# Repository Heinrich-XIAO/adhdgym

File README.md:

# adhdgym
adhdgym is a simple ultrasonic distance sensor that relays the distance to your computer at its simplest. It can be attatched to your cable machine to track your workouts. It comes with a web app that gamifies the experience of hitting your home gym. I made this because I kept being lazy in my workouts and not actualy liting the full amount, so having an app to keep track of this, and gamify this will probaby motivate me, or at least thats how i justify this.

## CAD

## PCB

## Schematics

## Client

## Build

https://youtube.com/shorts/1jzXrwt-IXw

## BOM
 - PCB and Case (I can 3D print myself)  $19.60 for pcb with jlc
 - 1x4 DuPont connector 2.54mm Socket (i think i have some)
 - Seeed XIAO ESP32-C3 https://www.seeedstudio.com/Seeed-XIAO-ESP32C3-p-5431.html  $24.40 (why is shipping so expensive :sob:)
 - DHT11 https://lcsc.com/product-detail/Temperature-and-Humidity-Sensor_Aosong-Guangzhou-Elec-DHT11_C117051.html?s_z=n_dht11 $18.43 (how is the cheapest shipping still $11.44 :sob::sob:)
 - HC-SR04 Module https://www.aliexpress.com/item/1005008259734214.html (if this link rots one day, just make sure to get one that has the pins on the non-speaker side) $2.65

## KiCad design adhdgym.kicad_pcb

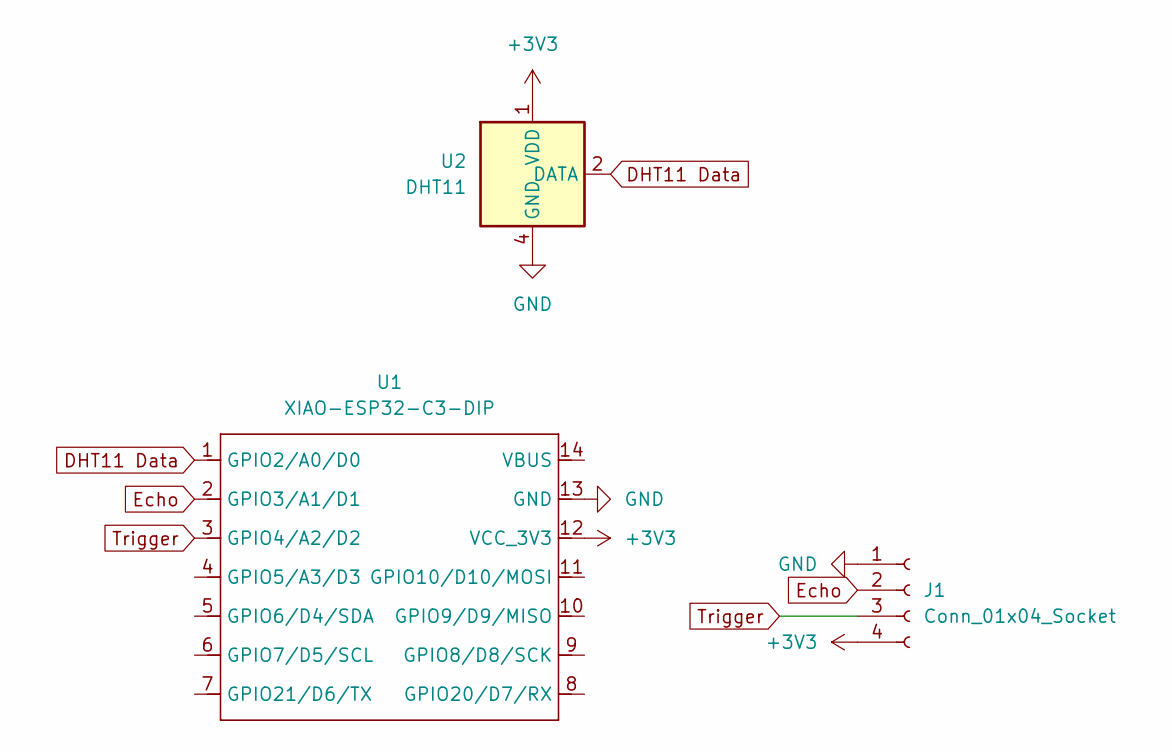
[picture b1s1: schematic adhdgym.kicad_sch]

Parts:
J1: Conn_01x04_Socket; PinSocket_1x04_P2.54mm_Vertical
U1: XIAO-ESP32-C3-DIP; MCU_Seeed_ESP32C3
U2: DHT11; Aosong_DHT11_5.5x12.0_P2.54mm

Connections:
+3V3: J1.4, U1.12 (VCC_3V3), U2.1 (VDD)
DHT11 Data: U1.1 (GPIO2/A0/D0), U2.2 (DATA)
Echo: J1.2, U1.2 (GPIO3/A1/D1)
GND: J1.1, U1.13 (GND), U2.4 (GND)
Trigger: J1.3, U1.3 (GPIO4/A2/D2)

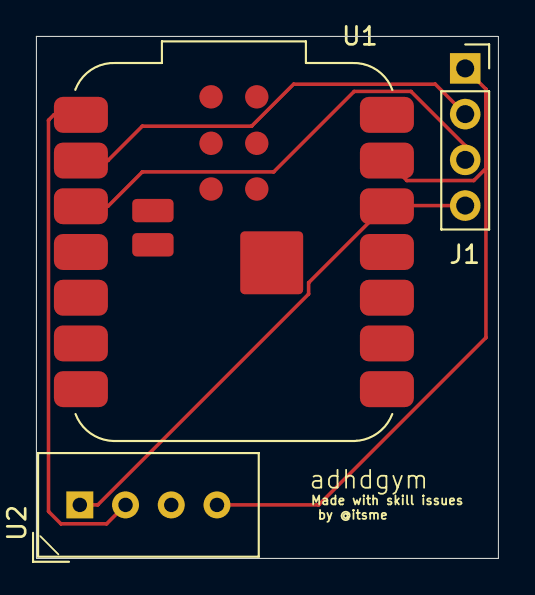
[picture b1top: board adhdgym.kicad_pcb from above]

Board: 2 copper layers, 25.7 x 29.0 mm, 3 parts (0 on the bottom side), 5 nets.

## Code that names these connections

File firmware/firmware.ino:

#include <Arduino.h>
#include <DHT.h>
#include <BLEDevice.h>
#include <BLEServer.h>
#include <BLEUtils.h>
#include <BLE2902.h>

// Pins
#define DHTPIN       2   // GPIO2 (A0/D0)
#define DHTTYPE      DHT11
#define TRIG_PIN     4   // GPIO4 (A2/D2)
#define ECHO_PIN     3   // GPIO3 (A1/D1)

// BLE UUIDs
#define SERVICE_UUID        "1f45750b-771b-460b-92ca-fdc00d263aee"
#define CHARACTERISTIC_UUID "064805b7-1272-436b-9683-a94509066057"

// Globals
DHT dht(DHTPIN, DHTTYPE);
BLECharacteristic* pCharacteristic;

// Speed of sound
// = 331 + 0.6 * T (in m/s), T = temp in C (proud canadian)
float calculateDistance(float temperatureC) {
  digitalWrite(TRIG_PIN, LOW);
  delayMicroseconds(2);
  digitalWrite(TRIG_PIN, HIGH);
  delayMicroseconds(10);
  digitalWrite(TRIG_PIN, LOW);

  long duration = pulseIn(ECHO_PIN, HIGH, 30000);
  float speed_of_sound = 331.0 + 0.6 * temperatureC; // m/s
  float distance_cm = (duration / 1e6) * speed_of_sound * 100 / 2;

  return distance_cm;
}

void setup() {
  Serial.begin(115200);
  delay(1000);

  // Init DHT
  dht.begin();

  // Init Ultrasonic pins
  pinMode(TRIG_PIN, OUTPUT);
  pinMode(ECHO_PIN, INPUT);

  // Init BLE
  BLEDevice::init("adhdgym");
  BLEServer *pServer = BLEDevice::createServer();
  BLEService *pService = pServer->createService(SERVICE_UUID);
  pCharacteristic = pService->createCharacteristic(
    CHARACTERISTIC_UUID,
    BLECharacteristic::PROPERTY_READ |
    BLECharacteristic::PROPERTY_NOTIFY
  );
  pCharacteristic->addDescriptor(new BLE2902());
  pService->start();

  BLEAdvertising *pAdvertising = BLEDevice::getAdvertising();
  pAdvertising->addServiceUUID(SERVICE_UUID);
  pAdvertising->start();

  Serial.println("BLE and stuff ready!");
}

void loop() {
  float temp = dht.readTemperature();

  if (isnan(temp)) {
    Serial.println("DHT read failed. bruh");
    return;
  }

  float distance = calculateDistance(temp);

  char buf[50];
  snprintf(buf, sizeof(buf), "Temp: %.1f C, Dist: %.1f cm", temp, distance);
  Serial.println(buf);

  // Send BLE
  pCharacteristic->setValue(buf);
  pCharacteristic->notify();

  delay(2000);
}

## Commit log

2025-06-11 pcb and scematics done. yay. procrastinated on homework.
2025-06-11 readme has desc now
2025-06-12 journal add top part
2025-06-12 Make journal look better
2025-06-14 journal update
2025-06-14 cad files
2025-06-14 Add Screenshots and BOM
2025-06-14 firmware written prob is completely broken still have to write client
2025-06-14 actually name the ble device
2025-06-15 i cant believe i just committed and pushed to main with this many typos
2025-06-15 add total time to journal
2025-06-15 Update README.md to include reason for making
2025-06-15 client
2025-06-15 add post shipping prices
2025-06-29 stuff
2025-06-29 fix stuff
2025-06-29 more stuff (need to name commits better
2025-06-29 make slider fine
2025-06-30 smoothing
2025-06-30 adjust smoothing factor
2025-06-30 feat: add preset feature to client
    Adds a preset feature to the client that allows users to save, load, and delete presets for frequency, amplitude, and offset values.
    The presets are stored in the browser's local storage.
2025-06-30 refactor: improve UI and amplitude calculation
    - Adds a label for the offset slider for better user experience.
    - Adjusts the amplitude calculation to be centered on the screen.
2025-06-30 fix: remove invalid characters and add missing label
2025-07-01 fix: remove invalid characters from script
2025-07-01 feat: increase dumbbell hitbox size
2025-07-01 feat: increase distance between dumbbell weights
2025-07-01 feat: make dumbbell thicker
2025-09-12 Add Build section with image to README
    Added build section with image to README.
2025-09-12 Add YouTube link to Build section in README
    Added a YouTube link to the Build section.
